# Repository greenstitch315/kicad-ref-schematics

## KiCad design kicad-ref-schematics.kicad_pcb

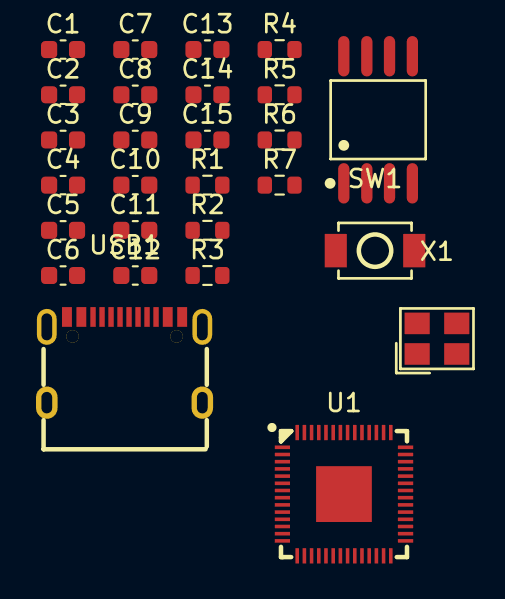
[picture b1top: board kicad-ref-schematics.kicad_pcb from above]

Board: 2 copper layers, 27 parts (0 on the bottom side), 21 nets, no tracks yet.

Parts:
C1, C2: 30p; C_0603_1608Metric
C3, C4, C5, C6, C7, C8, C9, C10, C13, C14, C15: 100n; C_0603_1608Metric
C11, C12: 1u; C_0603_1608Metric
R1, R4: 1k; R_0603_1608Metric
R2, R3: 27R; R_0603_1608Metric
R5: 10k; R_0603_1608Metric
R6, R7: 5k1; R_0603_1608Metric
SW1: TS-1088-AR02016; SW-SMD_L3.9-W3.0-P4.45
U1: RP2040; LQFN-56_L7.0-W7.0-P0.4-EP
U2: W25Q128JVSIQTR; SOIC-8_L5.3-W5.3-P1.27-LS8.0-BL
USB1: TYPE-C 16PIN 2MD(073); USB-C-SMD_TYPE-C-6PIN-2MD-073
X1: X322512MSB4SI; CRYSTAL-SMD_4P-L3.2-W2.5-BL

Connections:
+1V1: C12.1, C13.1, C14.1, U1.23 (DVDD), U1.45 (VREG_VOUT), U1.50 (DVDD)
+3.3V: C3.1, C4.1, C5.1, C6.1, C7.1, C8.1, C9.1, C10.1, C11.1, R5.1, U1.1 (IOVDD), U1.10 (IOVDD), U1.22 (IOVDD), U1.26 (RUN), U1.33 (IOVDD), U1.42 (IOVDD), U1.43 (ADC_AVDD), U1.44 (VREG_IN), U1.48 (USB_VDD), U1.49 (IOVDD)
+5V: USB1.2 (VBUS), USB1.11 (VBUS)
/rp2040/DN: R3.1, U1.46 (USB_DM)
/rp2040/DP: R2.1, U1.47 (USB_DP)
/rp2040/QSPI_SCLK: U1.52 (QSPI_SCLK), U2.6 (CLK)
/rp2040/QSPI_SD0: U1.53 (QSPI_SD0), U2.5 (DI)
/rp2040/QSPI_SD1: U1.55 (QSPI_SD1), U2.2 (DO)
/rp2040/QSPI_SD2: U1.54 (QSPI_SD2), U2.3 (IO2)
/rp2040/QSPI_SD3: U1.51 (QSPI_SD3), U2.7 (IO3)
/rp2040/QSPI_SS: U1.56 (QSPI_SS), U2.1 (~CS)
/rp2040/XIN: C1.2, U1.20 (XIN), X1.3 (OSC2)
/rp2040/XOUT: R1.2, U1.21 (XOUT)
GND: C1.1, C2.1, C3.2, C4.2, C5.2, C6.2, C7.2, C8.2, C9.2, C10.2, C11.2, C12.2, C13.2, C14.2, C15.2, R6.1, R7.1, SW1.1, U1.19 (TESTEN), U1.57 (GND), U2.4 (GND), USB1.1 (GND), USB1.12 (GND)
unnamed: R4.2, SW1.2
unnamed: C15.1, R4.1, R5.2, U2.8 (VCC)
unnamed: R7.2, USB1.4 (CC1)
unnamed: R6.2, USB1.10 (CC2)
unnamed: R3.2, USB1.5 (DN2), USB1.7 (DN1)
unnamed: R2.2, USB1.6 (DP1), USB1.8 (DP2)
unnamed: C2.2, R1.1, X1.1 (OSC1)

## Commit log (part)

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2026-02-04 Add project files
2026-02-04 Tidy wiring
2026-02-06 Organise capacitors
